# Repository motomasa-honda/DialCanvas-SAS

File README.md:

# DialCanvas-SAS / Forest Guardian

このリポジトリは、Forest Guardian / DialCanvas Desk Edition の設計とソフトウェアを管理します。旧DialCanvas腕時計資料と旧7軸置き時計設計は、由来を残すため履歴として保持しています。

## 現行設計

- [新設計の基準](docs/10-desk-redesign/README.md)：ウォールナット筐体、円形画面、microSD文字盤、単一モーターで連動する装飾歯車。
- [要求台帳](docs/01-requirements/requirements.yaml)：状態付き要求、未決定事項、検証項目。
- [現状と証拠](docs/10-desk-redesign/status-2026-10-21.md)：確認済みソース、ホスト試験、未実施の実機検証。
- [残作業一覧](docs/10-desk-redesign/worklist.csv)：各項目の状態と完了条件。
- [要求移行表](docs/10-desk-redesign/requirements-migration-v0.8-to-v0.21.csv)：旧7軸要求から現行v0.21要求への対応。

現行方針は7軸固定ではなく、歯車数も固定しません。現時点の28歯車図は配置候補です。TMC2209、Waveshare 3.4C、モーター、電源、材料も、実物と安全条件を受け入れるまでは候補です。

## ソフトウェア

- `firmware/cots_clock_core/`：針角度、エンコーダー、文字盤選択、ステッパー周期、DS3231 UTC変換のホスト検証可能なCコア。
- `firmware/cots_clock_app/`：ESP-IDF/LVGLアプリ。文字盤表示、microSD走査、操作、時刻同期、RTC処理を含みます。モーターGPIO出力は明示的なビルド設定がない限り無効です。
- ホストテストとESP-IDFビルドは `.github/workflows/desk-redesign.yml` で実行します。

ホスト試験成功は実基板のGPIO割当、表示性能、RTC保持、電源安全、歯車負荷、騒音、温度を証明しません。製作・購入・通電・書込みの受入状態は作業一覧を参照してください。

## 旧設計資料

`execution/` と旧設計向け文書・回路・ブランチはその時点の証拠を保つため残しています。現行の進捗率や新設計の合格根拠には使用しません。旧ブランチは更新しません。

## 設計文書の整合性確認

```sh
python3 tests/check_design.py
cmake -S firmware/cots_clock_core -B /tmp/dialcanvas-clock-core-build
cmake --build /tmp/dialcanvas-clock-core-build
ctest --test-dir /tmp/dialcanvas-clock-core-build --output-on-failure
```

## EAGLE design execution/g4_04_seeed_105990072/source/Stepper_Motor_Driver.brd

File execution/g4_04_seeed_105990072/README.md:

# Seeed 105990072 source-CAD review

## Result

The vendor EAGLE source contains a panelized board file. Parsing the smallest closed layer-20 outline enclosing the populated circuit gives a **nominal PCB envelope of 35.0 × 19.3 mm**. The 50 × 41 mm per-axis reservation therefore leaves a centered bare-PCB clearance of 7.5 mm per side in X and 10.85 mm per side in Y. The motor driver board has **no mounting holes inside its PCB outline**.

The separately published motor drawing identifies model `CX28BYJ48-08`: body Ø28±0.1 mm, two mounting holes Ø4.2±0.15 mm at 35±0.2 mm centers, body depth 19.1±0.2 mm, shaft Ø5±0.1 mm with 13.5±0.2 mm projection, and Ø9±0.2 mm shaft boss. The factory lead is shown as 250±10 mm, UL1061 26AWG. These are source drawing dimensions, not measured incoming parts.

## Motor fit against the existing axis reservation

`check_axis_envelope.py` derives a conservative plan envelope from the drawing's maximum hole-center spacing plus maximum hole diameter, and the maximum body diameter. The resulting motor envelope is **39.55 × 28.10 mm**. When aligned with the existing 40 × 31 mm axis cassette candidate, the 35 mm mounting-hole direction must run along the 50 mm reservation axis: the nominal margin is only **0.225 mm** on each side within the 40 mm dimension and **1.45 mm** within 31 mm. Rotating it 90° exceeds the 31 mm cassette dimension by 8.55 mm. The complete 50 × 41 mm reservation still has at least 5 mm nominal margin around the selected motor orientation.

The driver PCB (35.0 × 19.3 mm) separately fits within 40 × 31 mm, with 2.5 mm and 5.85 mm margins per side. These are overlapping XY projections of two different parts: the motor and driver board need a real Z-stack/bracket layout. The 0.225 mm margin is consumed by ordinary mounting hardware and cannot serve as a fastener or tool allowance. This result sets an orientation constraint and identifies a cassette packaging conflict; it does not establish motor retention, a manufacturable bracket, tolerance capability, or the required 55 mm exchange path. The next mechanical model must fit the motor fixing hardware and independently retained driver board inside the unchanged 50 × 41 mm reserve, then rerun the D7 sweep.

## Motor fixing-plate candidate

`MOTOR_MOUNT_PLATE_CANDIDATE.scad` is a first parametric datum-plate study sized 48 × 39 mm within the existing 50 × 41 mm per-axis reservation. It places the 35 mm motor mounting span along the 50 mm axis, uses 4.8 mm candidate slots with ±0.4 mm local center travel, and a 10 mm center opening against the drawing's maximum 9.2 mm shaft boss. `check_mount_candidate.py` validates those arithmetic bounds against the archived source dimensions and emits `mount_candidate_screen.json`.

This makes a motor face-plate geometrically plausible within the reservation, but does not fit the separate 35 × 19.3 mm driver PCB: the two remain overlapping XY projections. PCB edge retention, Z-stack, screw-head/washer/tool envelopes, plate material/thickness/strength, motor-to-gear coupler, D7 55 mm sweep, and process tolerances remain unqualified. The SCAD file is a review candidate only; no fastener or machining dimensions are released.

### Driver-board edge-window screen

`check_board_edge_capture.py` parses the archived EAGLE package tPlace line/circle proxies and through-hole/SMD copper bounds for the populated-board components, then checks two candidate edge-lip contact windows with a 0.30 mm planar clearance. `BOARD_EDGE_CAPTURE_REVIEW.scad` is a visual locator for those windows; it is not the vendor 3D geometry and must not be used as a finished retainer. `test_board_edge_capture.py` injects a deliberate copper collision and a clear case to verify the screen rejects/accepts the expected cases. The generated `board_edge_capture_screen.json` records source hash, bounds, and limitations.

Both windows clear the selected source proxies and copper shapes. This only identifies candidate contact regions: the vendor source has no 3D courtyard/height data, and board thickness, solder projections, clip material/spring force, insertion path, cable exit, tools, vibration, motor-driver Z stack, and the D7 55 mm service sweep remain unchecked. No retaining clip geometry or manufacturing dimension is released. G4-04/FG-026 remain OPEN.

Run `python3 execution/g4_04_seeed_105990072/check_axis_envelope.py` to regenerate [`axis_envelope_screen.json`](axis_envelope_screen.json). It is a static drawing-based fit screen only.

The exact EAGLE footprints and board/schematic connectivity resolve the headers as follows. “IN1” through “IN4” refer to the ULN2003 input pins 1B through 4B respectively.

| Connector | Pad | Signal / connection | Pitch |
| --- | ---: | --- | ---: |
| J5 control | 1 | VM | 2.54 mm |
| J5 control | 2 | VCC / ULN2003 COM | 2.54 mm |
| J5 control | 3 | GND / ULN2003 E | 2.54 mm |
| J5 control | 4 | IN4 / ULN2003 4B | 2.54 mm |
| J5 control | 5 | IN3 / ULN2003 3B | 2.54 mm |
| J5 control | 6 | IN2 / ULN2003 2B | 2.54 mm |
| J5 control | 7 | IN1 / ULN2003 1B | 2.54 mm |
| J4 motor | 1 | VMOTOR | 2.54 mm |
| J4 motor | 2 | ULN2003 4C | 2.54 mm |
| J4 motor | 3 | ULN2003 3C | 2.54 mm |
| J4 motor | 4 | ULN2003 2C | 2.54 mm |
| J4 motor | 5 | ULN2003 1C | 2.54 mm |

The schematic device mapping explicitly maps J4 symbol pins `P$1`…`P$5` to footprint pads `1`…`5`, and J5 symbol pins `1`…`7` to footprint pads `1`…`7`. Thus J4 pad/net order is established from two independent source files: schematic pin → package pad → board contact/net → ULN2003 collector. In J4 package-local coordinates, pad 1 is at `(5.08, 0)` mm and pad 5 at `(-5.08, 0)` mm; the placed board element is rotated `R270`. This establishes the source-CAD pad identity and order, but it does not establish a user-facing viewing direction or the conductor colors on an as-received cable. Preserve the connector's keyed/latch orientation in the harness drawing and confirm every supplied conductor by continuity before fixing a wire-color-to-pad table.

J5 is the vendor `H7-2.54` seven-position through-hole footprint; J4 is the vendor `JST5-2.54` five-position through-hole footprint. The largest source pad drills are 0.889 mm (J5) and 0.8128 mm (J4). Verify the supplied cable and mating connector before choosing harness ends; the EAGLE footprint name does not identify the mating housing vendor or its retention force.

**Connector discrepancy:** the motor drawing calls out a white `XHP-5` housing at 2.5 mm pitch, while the driver board EAGLE J4 pad centers are 2.54 mm pitch. This is 0.04 mm per interval, or 0.16 mm across the first-to-fifth center distance. JST's XH catalog specifies the series as 2.5 mm pitch. Direct plug compatibility is therefore **not accepted** from the drawings alone. The low-risk design route is a documented short adapter harness or an exact connector replacement selected after confirming the supplied board revision; do not force the motor plug onto the board header.

## Scope and remaining acceptance

The archived vendor files, extracted board and schematic, SHA-256 evidence, and deterministic parser are kept here. Run:

```sh
python3 execution/g4_04_seeed_105990072/check_vendor_cad.py
```

This is a static parse of the vendor source, not proof that a purchased production unit has the same revision or dimensions. The no-hole board needs a removable edge-capture or pocket in each axis cassette. That retention must preserve independent service access and avoid stressing solder joints. Connector insertion/removal clearance and wire bend radius must be added outside the bare-board rectangle. The 35 mm motor mount span and 35 mm PCB width both approach the 44 mm sled width; retain the motor's Ø3.5 mm lug radii, Ø4.2 mm holes, fastener washers, wall thickness, tool access, and gear-shaft alignment in the next local CAD pass. Actual received-unit dimensions, shaft/coupler fit, loaded torque/current/temperature, noise, and seven-axis operation remain unverified.

Status remains **G4-04 OPEN / FG-026 OPEN / G3-08 HARDWARE_WAIT**. No part has been ordered, powered, fabricated, or approved for manufacturing. Motor enable and driver OE remain inhibited.

## Source provenance

- Manufacturer page and linked CAD archive: <https://wiki.seeedstudio.com/Gear_Stepper_Motor_Driver_Pack/>
- Official JST XH 2.5 mm series catalog: <https://www.jst-mfg.com/product/pdf/eng/eXH.pdf>
- Direct archive URL and source checksums: [`cad_evidence.json`](cad_evidence.json)
- Vendor files are preserved under [`source/`](source/), without edits.

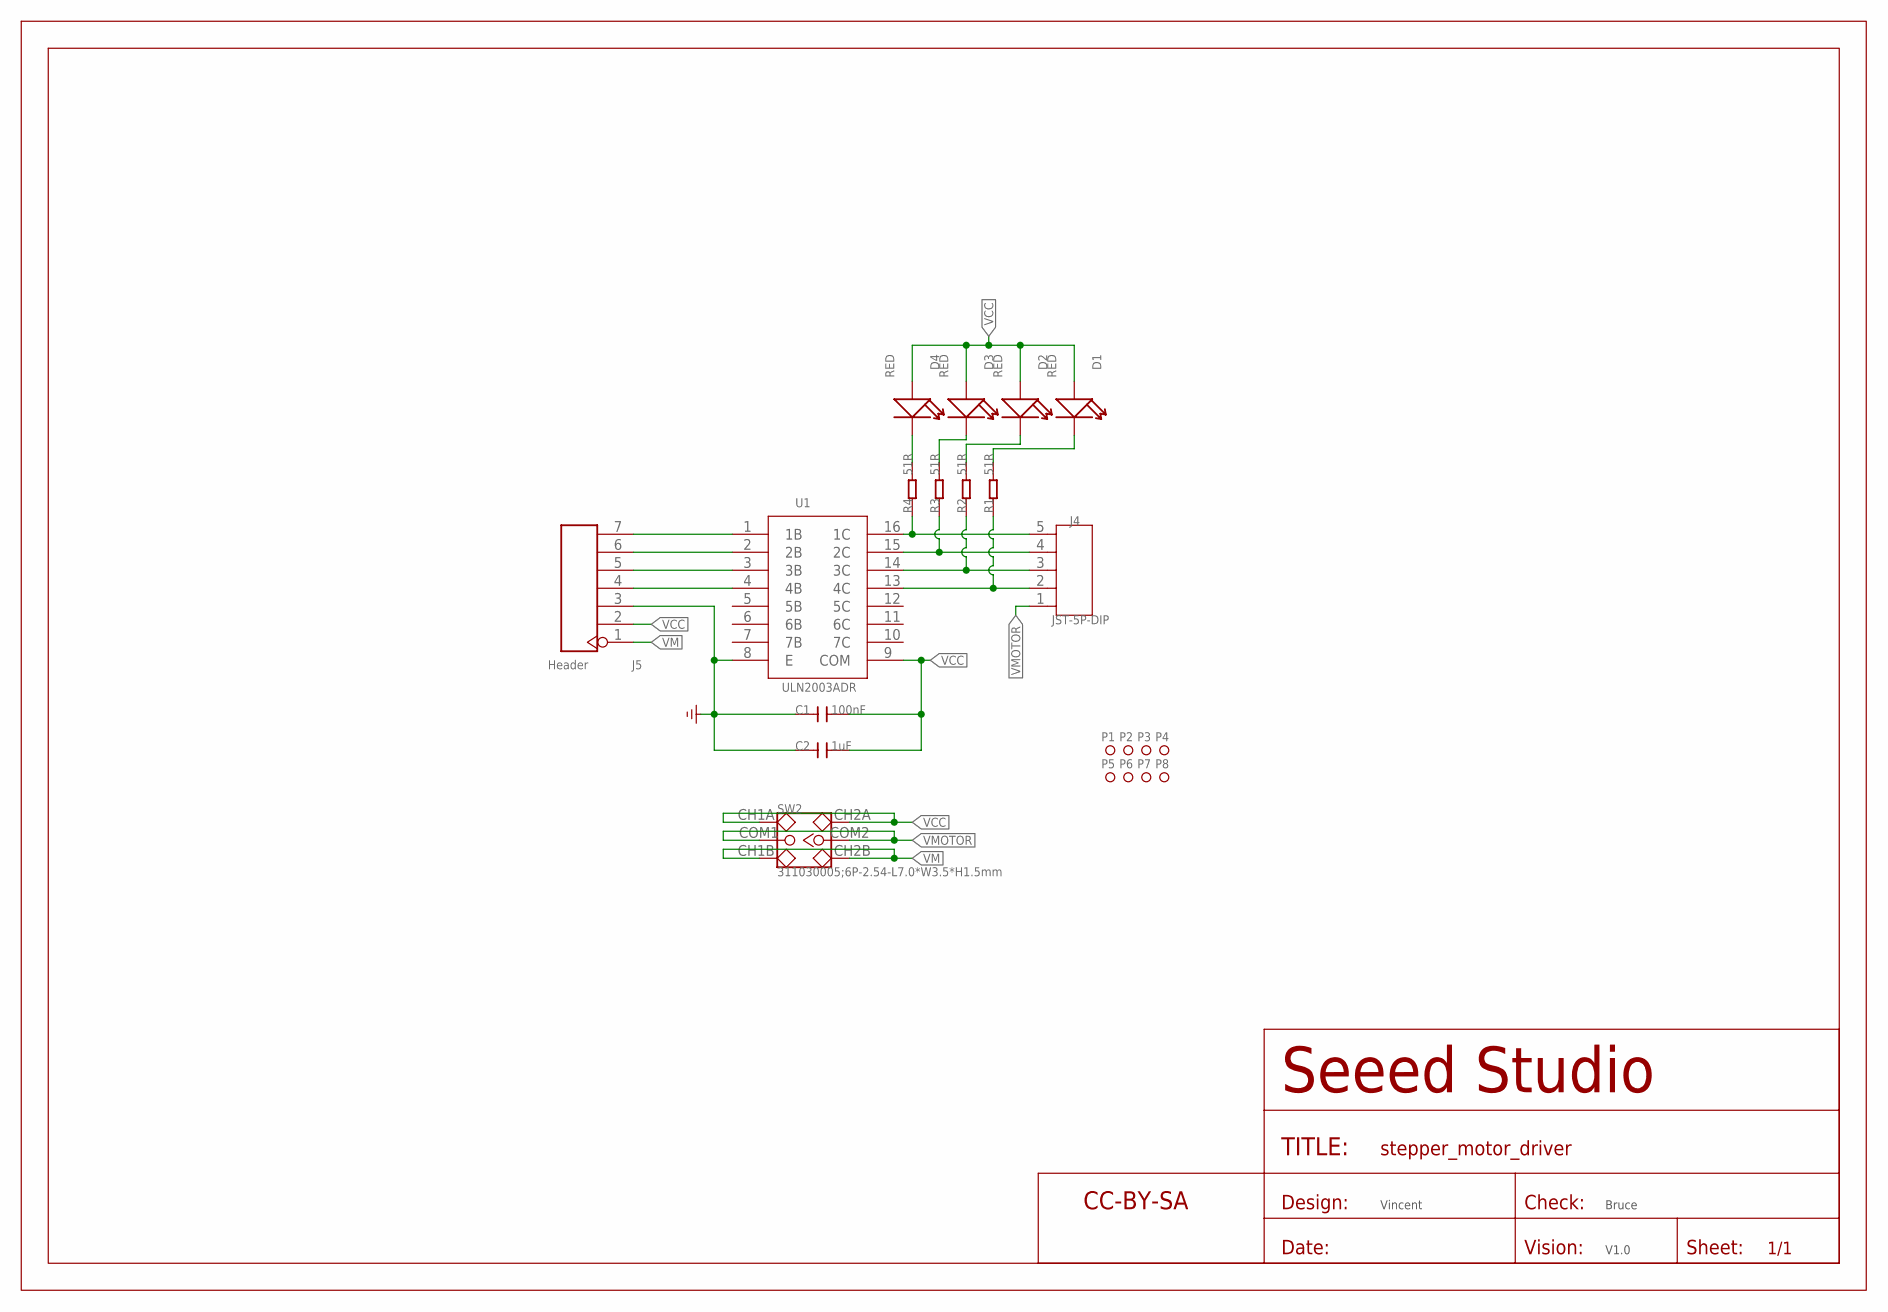
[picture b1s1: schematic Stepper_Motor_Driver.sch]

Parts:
C1: 100nF; C0603
C2: 1uF; C0603
D1, D2, D3, D4: RED; LED-0603
J4: JST-5P-DIP; JST5-2.54
J5: Header; H7-2.54
P1, P2, P3, P4, P5, P6, P7, P8: MARK-1.0'ANNULAR'; ROUND-MARK-1.0
R1, R2, R3, R4: 51R; R0603
SW2: 311030005;6P-2.54-L7.0*W3.5*H1.5mm; SW6-2.54-SMD-7.0X3.5X1.5MM
U1: ULN2003ADR; SOIC16-1.27-10X3.9MM
U$1: SEEEDSTUDIO-OPEN-SCH-FRAME; SEEEDSTUDIO-PCB-FRAME

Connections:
GND: C1.1, C2.1, J5.3, U1.8 (E)
unnamed: J4.4, R3.2, U1.15 (2C)
unnamed: J4.3, R2.2, U1.14 (3C)
unnamed: J5.4, U1.4 (4B)
unnamed: D4.-, R4.1
unnamed: J5.7, U1.1 (1B)
unnamed: J5.6, U1.2 (2B)
unnamed: J5.5, U1.3 (3B)
unnamed: D3.-, R3.1
unnamed: J4.5, R4.2, U1.16 (1C)
unnamed: D2.-, R2.1
unnamed: D1.-, R1.1
unnamed: J4.2, R1.2, U1.13 (4C)
VCC: C1.2, C2.2, D1.+, D2.+, D3.+, D4.+, J5.2, SW2.CH1A, SW2.CH2A, U1.9 (COM)
VM: J5.1, SW2.CH1B, SW2.CH2B
VMOTOR: J4.1, SW2.COM1, SW2.COM2

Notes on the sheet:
Vincent
V1.0
Bruce

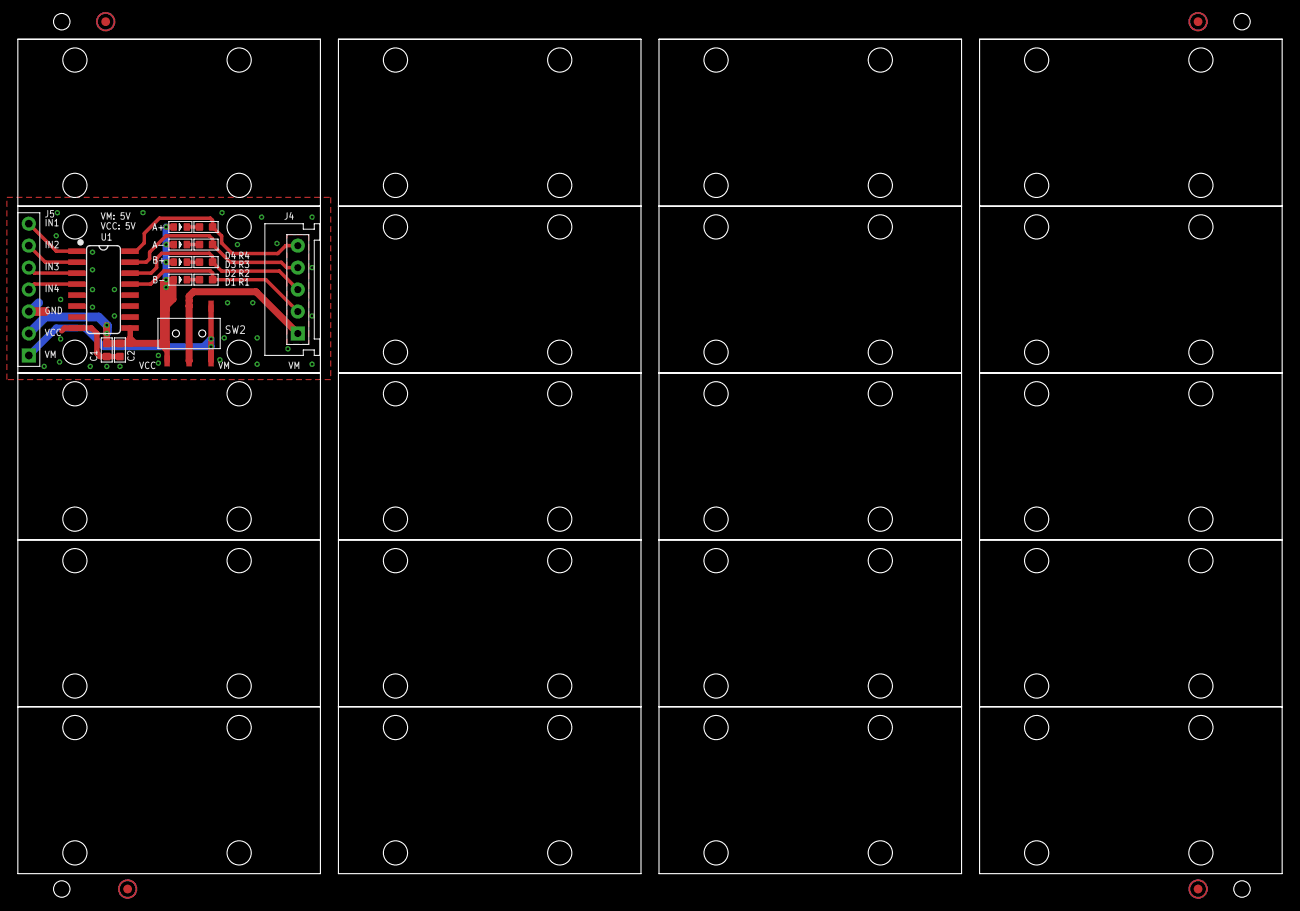
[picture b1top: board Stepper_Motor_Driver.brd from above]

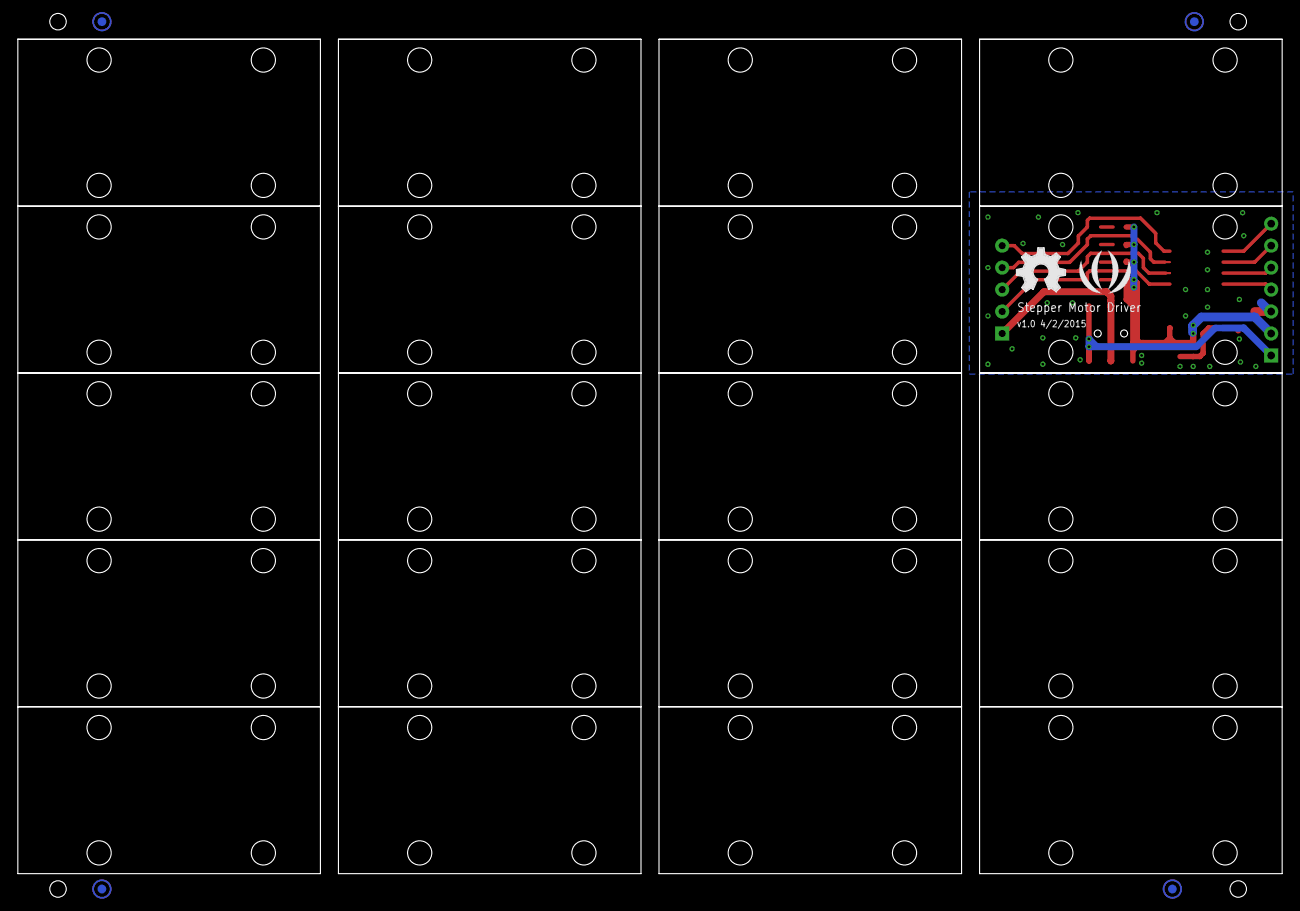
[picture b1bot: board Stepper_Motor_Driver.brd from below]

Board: 2 copper layers, 146.3 x 96.5 mm, 25 parts (6 on the bottom side), 16 nets.

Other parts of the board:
U$7: SEEED-SILK-280*268MIL
U$8: OSHW_FILLX200_NOTEXT

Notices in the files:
parts and their libraries:
moudle-new: This work is licensed under the Creative Commons Attribution 4.0 International License.
To view a copy of this license,visit:
http://creativecommons.org/licenses/by-sa/4.0
moudle-new: CC-BY-SA
